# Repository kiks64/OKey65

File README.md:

# Okey65 ortholinear keyboard
<br />This work is licensed under a <a rel="license" href="http://creativecommons.org/licenses/by-nc-sa/4.0/">Creative Commons Attribution-NonCommercial-ShareAlike 4.0 International License</a>.
### _A 65 keys ortholinear keyboard using a qwerty based symetric layout_

The goal of this project is to design an enhanced version of my hand-wired keyboard that I have been using for several years. 
The keyboard has a well-balanced size that allows it to be quite compact while still having all the important keys available on the main layer.
Its layout is quite atypical but very convenient for typing text with accented Latin characters.  

It is based on an Atmega32u4 chip and runs QMK. The switch footprints are 5-pins MX type.
The design is minimalist, not including backlight, but modern : the pcb has no screws and is fully dampened by EVA foam.  
However, not being an electronics professional and this project being my first one, the switches are not hot-swappable since integrating this feature makes the design too complex for my skill level.  

Before continuing, I would like to thank ai03 and Masterzen for their tutorials which made this project possible, as well as all the contributors of the QMK firmware.
<p align="center">
  <br />
  
  &nbsp; &nbsp;
  
</p>

### List of required parts

The keyboard consists of a top plate, a pcb and a bottom plate, all in fr4 and designed on Kicad, as well as a 3d printed frame in resin 8000 (sla) designed on Fusion 360. All these parts were ordered from JLCPCB.
I chose these materials for their reasonable cost, their lightness as well as to obtain a soft typing feeling.   

All the electronic components come from Digikey except the Atmel chip which comes from Aliexpress since it is out of stock at all specialist retailers. The BOM list therefore consists of component references available from Digikey.  

Regarding the switches, I chose Gateron Pro Milky Yellow for their price, their softness and because they are stock lubed, which saves me laborious work.  

Finally, I reused the keycaps from my previous hand-wired keyboard because they come from Signature Plastics and are very expensive.
It is difficult to find a keyset that is perfectly compatible with this keyboard because the caps have to be non sculpted (dsa or xda) and ortholinear sets lack keycaps since they are designed for the Plank and Preonic which are smaller than my keyboard.  

Apart from the Signature Plastics solution, I found two sets that fit perfectly :   
A simple set, entirely white, inexpensive and available immediately: https://fr.aliexpress.com/item/1005003174191494.html (version white with legend)  
If you are not in a hurry, a magnificent set, more expensive and rarely available: https://drop.com/buy/massdrop-x-mito-canvas-xda-custom-keycap-set (alphas/betas set + text ortho/micons ortho set)  

**Aditionnal stuff you will need :**  
An USB type C cable.  
Spray paint and plastic primer : I used Montana Colors mtn94 paint, nice quality, easy to use.  
M2 brass standoffs 10mm : https://aliexpress.com/item/4000314663724.html (fit perfectly).  
M2 flat head screws 10mm : https://aliexpress.com/item/4001072025844.html  
Foam tapes 1x12mm + 3x8mm : https://aliexpress.com/item/33012825553.html  
Foam sheets  2mm : I used this item https://aliexpress.com/item/1005002856054113.html but it is more dense than I expected, maybe not the best option.  
A Double-sided adhesive tape.  
A syringe of solder paste (preferably T5 grade because the usb type c port is tricky to solder) as well as solder wire.  
A hot air rework station, a solder iron, tweezers, a magnifying glass and a cutting tool.  
A lot of patience :)  

### Assembly guide  

To start, heat the frame with a hair dryer and then insert the spacers into it. Once cool, the spacers will be tight enough, no need to add glue.  
Then take care of painting the frame and let it dry well.Sanding may be required before painting.  
Then place the 1mm adhesive foam strip inside the frame as shown in the photo below. 

Cut out the different foams using the top plate and bottom plate as templates :  
Between the top plate and the pcb I used 2 sheets of 2mm that I glued together before cutting them. With 4mm of compact foam for a space between plates of 3mm, soldering the switches was very difficult because I had to compress the foam at the same time. Instead, try to find a sheet of 3mm foam or less dense foam.  
Same observation for the foam between the pcb and the bottom plate, 4mm if good but EVA foam is definitely too dense and it was difficult to close the case the first time.  
A last sheet of 2mm foam glued under the bottom plate as a sole. Here, EVA is perfect and provides a good support for the keyboard and prevents the screw heads from touching the desk.  
Finally, cut strips of 3mm wide and thick self-adhesive foam and stick them all around the top plate.
<p align="center">
  <br />
  
  &nbsp; &nbsp;
  
</p>  

Now it's time to solder the components on the pcb.  
Leave the components in their bag until it is time to place them on the solder paste and be sure of their correct placement. Once out of their bag, it is very difficult to differentiate them so be careful!  
You will have 5 pcb, so also have some spare components in case it goes wrong. If you do not know how to use a hot air station, I advise you to find out before you start.  

Start with the usb receptacle which is the hardest part to solder because the pins are very close. Use very little solder paste to avoid making bridges which are very hard to see and remove.
Do not forget to secure the fixing of the usb receptacle by soldering the through tabs with a soldering iron and soldering wire  
Do the same for the Atmel chip, but this time it's easier and you can put a little more solder paste.  
Finally, put solder paste on all the remaining pads and arrange all your smd components, taking care to respect the polarity of the diodes, and solder them all at the same time.  

Check your welds with a magnifying glass and use a multimeter to check that there are no bridges.  
If everything is ok, it's time to flash the firmware. Instructions are available in the README file of the firmware's folder.  

Finally comes the step of soldering the switches, don't forget the foam between the top plate and the pcb ;)  
Start by soldering a switch at each corner, then one or two in the middle. After that, place all the switches and solder them.  

Plug in your keyboard to test all the keys. If a whole row or column does not work, check that all the pins of the chip are well soldered. If an isolated key does not work, it is likely that the polarities of the associated diode are reversed.  

If everything works, all you have to do is insert the assembly into the frame, add the 4mm foam, place the bottom plate and screw it gently.  
Finally install the caps, connect the usb cable and enjoy!  
If you plan to use accents, set your computer's input method to US International.
  <p align="center">
  <br />
  
  &nbsp; &nbsp;
  
</p>  
<p align="center">
  
  &nbsp; &nbsp;
  
</p>  

Using a wrist rest greatly improves comfort and ergonomics.
I made one with some EVA foam, double sided tape and cloth, the dimensions are 300x80x15mm and that's fine, a little longer would be perfect, like 320-350mm.

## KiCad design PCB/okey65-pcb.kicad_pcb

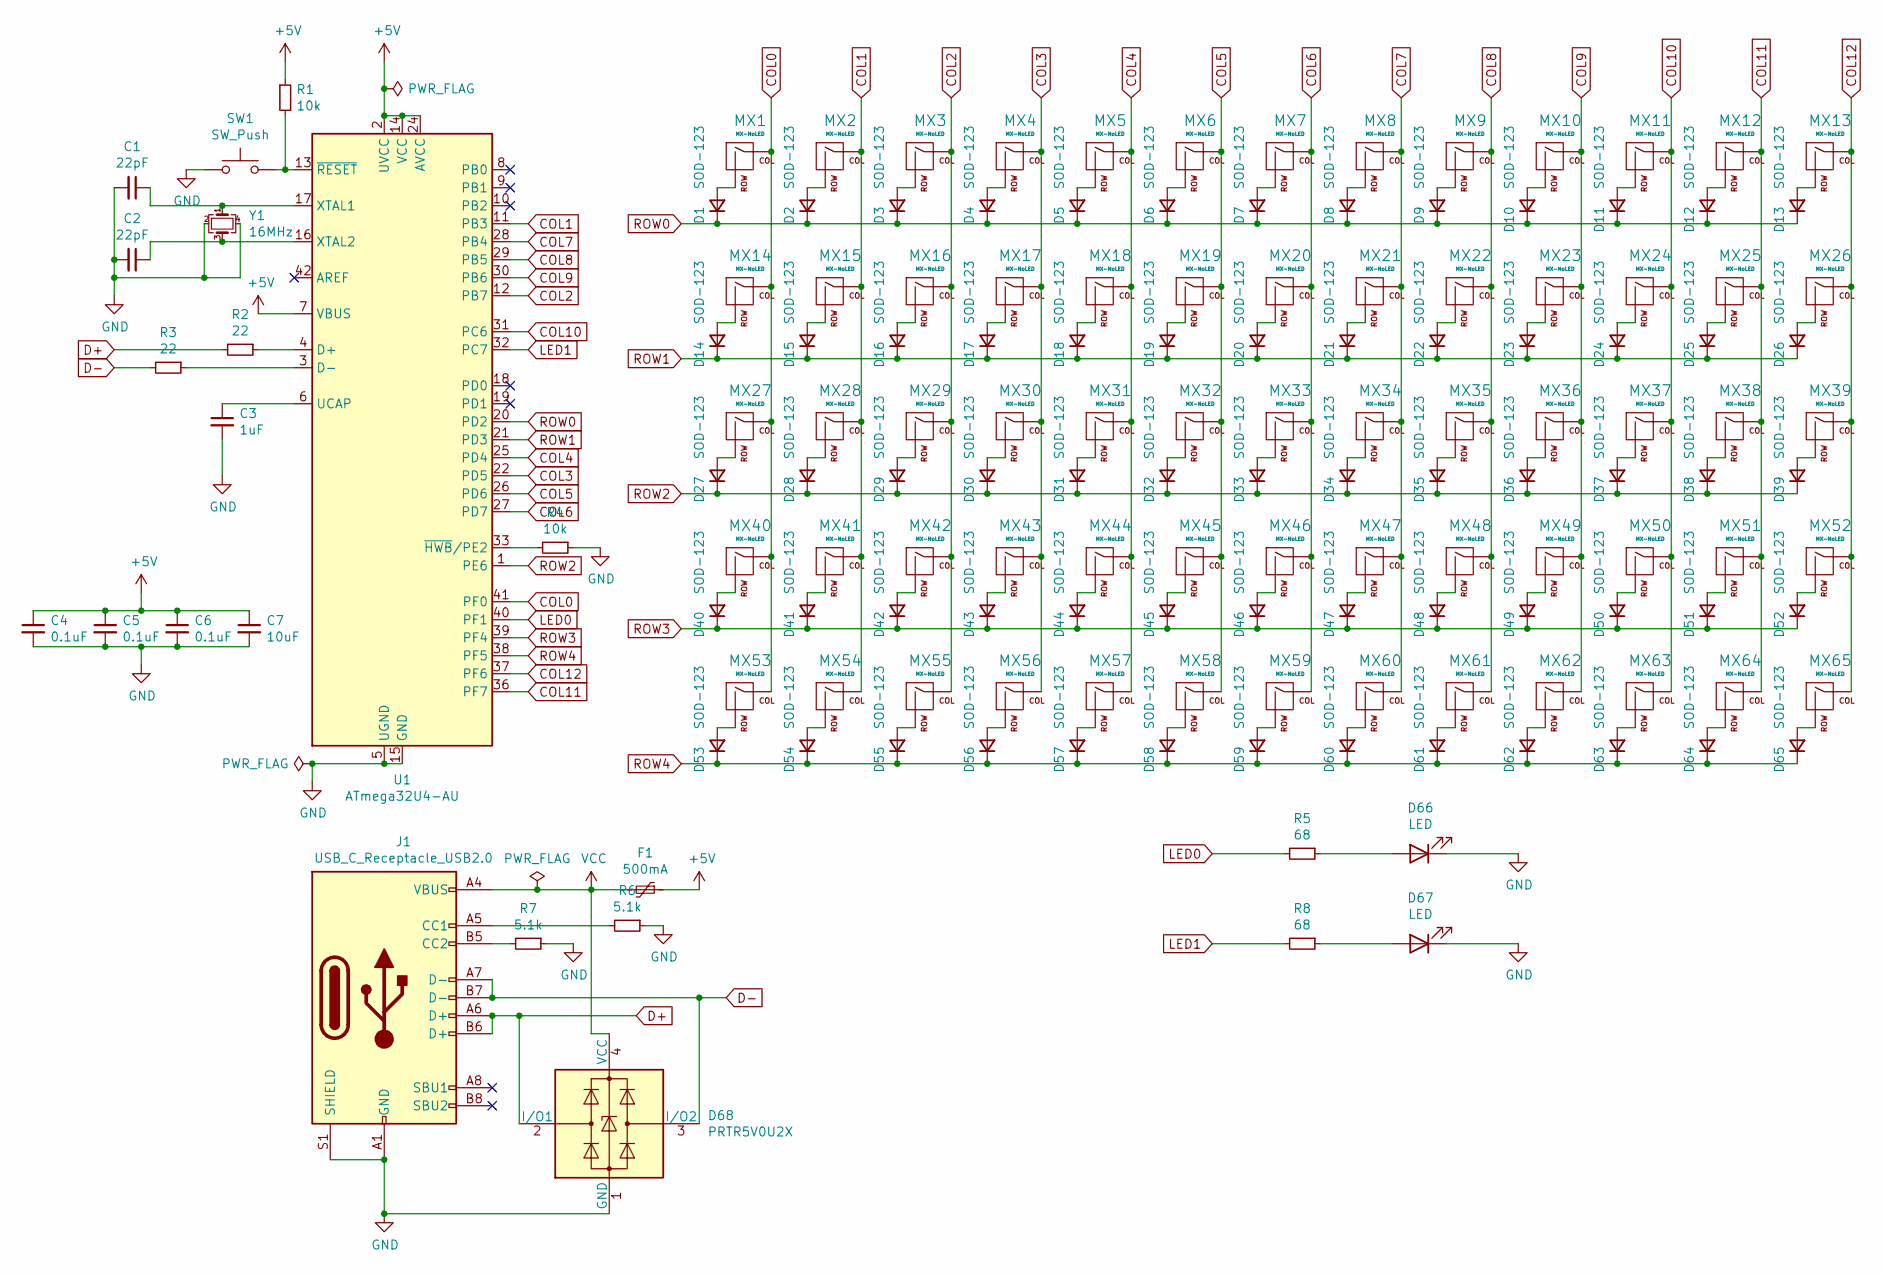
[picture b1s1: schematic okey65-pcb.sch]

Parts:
C1, C2: 22pF; C_0805_2012Metric; LCSC C1804
C3: 1uF; C_0805_2012Metric; LCSC C116352
C4, C5, C6: 0.1uF; C_0805_2012Metric; LCSC C286511
C7: 10uF; C_1206_3216Metric; LCSC C77075
D1, D2, D3, D4, D5, D6, D7, D8, D9, D10, D11, D12, D13, D14, D15, D16, D17, D18, D19, D20, D21, D22, D23, D24, D25, D26, D27, D28, D29, D30, D31, D32, D33, D34, D35, D36, D37, D38, D39, D40, D41, D42, D43, D44, D45, D46, D47, D48, D49, D50, D51, D52, D53, D54, D55, D56, D57, D58, D59, D60, D61, D62, D63, D64, D65: SOD-123; D_SOD-123; LCSC C81598
D66, D67: LED; LED_1206_3216Metric_ReverseMount_Hole1.8x2.4mm; LCSC C401114
D68: PRTR5V0U2X; SOT143B
F1: 500mA; Fuse_1206_3216Metric; LCSC C883125
J1: USB_C_Receptacle_USB2.0; USB_C_Receptacle_Palconn_UTC16-G; LCSC C136423
MX1, MX2, MX3, MX4, MX5, MX6, MX7, MX8, MX9, MX10, MX11, MX12, MX13, MX14, MX15, MX16, MX17, MX18, MX19, MX20, MX21, MX22, MX23, MX24, MX25, MX26, MX27, MX28, MX29, MX30, MX31, MX32, MX33, MX34, MX35, MX36, MX37, MX38, MX39, MX40, MX41, MX42, MX43, MX44, MX45, MX46, MX47, MX48, MX49, MX50, MX51, MX52, MX53, MX54, MX55, MX56, MX57, MX58, MX59, MX60, MX61, MX62, MX63, MX64, MX65: MX-NoLED; MXOnly-1U-NoLED
R1, R4: 10k; R_0805_2012Metric; LCSC C406725
R2, R3: 22; R_0805_2012Metric; LCSC C25295
R5, R8: 68; R_0805_2012Metric; LCSC C17802
R6, R7: 5.1k; R_0805_2012Metric; LCSC C27834
SW1: SW_Push; SKQG-1155865; LCSC C221929
U1: ATmega32U4-AU; TQFP-44_10x10mm_P0.8mm; LCSC C44854
Y1: 16MHz; Crystal_SMD_3225-4Pin_3.2x2.5mm; LCSC C213410

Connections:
+5V: C4.1, C5.1, C6.1, C7.1, F1.1, R1.1, U1.2 (UVCC), U1.7 (VBUS), U1.14 (VCC), U1.24 (AVCC), U1.34 (VCC), U1.44 (AVCC)
COL0: MX1.1 (COL), MX14.1 (COL), MX27.1 (COL), MX40.1 (COL), MX53.1 (COL), U1.41 (PF0)
COL1: MX2.1 (COL), MX15.1 (COL), MX28.1 (COL), MX41.1 (COL), MX54.1 (COL), U1.11 (PB3)
COL2: MX3.1 (COL), MX16.1 (COL), MX29.1 (COL), MX42.1 (COL), MX55.1 (COL), U1.12 (PB7)
COL3: MX4.1 (COL), MX17.1 (COL), MX30.1 (COL), MX43.1 (COL), MX56.1 (COL), U1.22 (PD5)
COL4: MX5.1 (COL), MX18.1 (COL), MX31.1 (COL), MX44.1 (COL), MX57.1 (COL), U1.25 (PD4)
COL5: MX6.1 (COL), MX19.1 (COL), MX32.1 (COL), MX45.1 (COL), MX58.1 (COL), U1.26 (PD6)
COL6: MX7.1 (COL), MX20.1 (COL), MX33.1 (COL), MX46.1 (COL), MX59.1 (COL), U1.27 (PD7)
COL7: MX8.1 (COL), MX21.1 (COL), MX34.1 (COL), MX47.1 (COL), MX60.1 (COL), U1.28 (PB4)
COL8: MX9.1 (COL), MX22.1 (COL), MX35.1 (COL), MX48.1 (COL), MX61.1 (COL), U1.29 (PB5)
COL9: MX10.1 (COL), MX23.1 (COL), MX36.1 (COL), MX49.1 (COL), MX62.1 (COL), U1.30 (PB6)
COL10: MX11.1 (COL), MX24.1 (COL), MX37.1 (COL), MX50.1 (COL), MX63.1 (COL), U1.31 (PC6)
COL11: MX12.1 (COL), MX25.1 (COL), MX38.1 (COL), MX51.1 (COL), MX64.1 (COL), U1.36 (PF7)
COL12: MX13.1 (COL), MX26.1 (COL), MX39.1 (COL), MX52.1 (COL), MX65.1 (COL), U1.37 (PF6)
D+: D68.2 (I/O1), J1.A6 (D+), J1.B6 (D+), R2.2
D-: D68.3 (I/O2), J1.A7 (D-), J1.B7 (D-), R3.2
LED0: R5.2, U1.40 (PF1)
LED1: R8.2, U1.32 (PC7)
unnamed: C1.1, U1.17 (XTAL1), Y1.1
unnamed: C2.1, U1.16 (XTAL2), Y1.3
unnamed: C3.1, U1.6 (UCAP)
unnamed: D1.2 (A), MX1.2 (ROW)
unnamed: D2.2 (A), MX2.2 (ROW)
unnamed: D3.2 (A), MX3.2 (ROW)
unnamed: D4.2 (A), MX4.2 (ROW)
unnamed: D5.2 (A), MX5.2 (ROW)
unnamed: D6.2 (A), MX6.2 (ROW)
unnamed: D7.2 (A), MX7.2 (ROW)
unnamed: D8.2 (A), MX8.2 (ROW)
unnamed: D9.2 (A), MX9.2 (ROW)
unnamed: D10.2 (A), MX10.2 (ROW)
unnamed: D11.2 (A), MX11.2 (ROW)
unnamed: D12.2 (A), MX12.2 (ROW)
unnamed: D13.2 (A), MX13.2 (ROW)
unnamed: D14.2 (A), MX14.2 (ROW)
unnamed: D15.2 (A), MX15.2 (ROW)
unnamed: D16.2 (A), MX16.2 (ROW)
unnamed: D17.2 (A), MX17.2 (ROW)
unnamed: D18.2 (A), MX18.2 (ROW)
unnamed: D19.2 (A), MX19.2 (ROW)
unnamed: D20.2 (A), MX20.2 (ROW)
unnamed: D21.2 (A), MX21.2 (ROW)
unnamed: D22.2 (A), MX22.2 (ROW)
unnamed: D23.2 (A), MX23.2 (ROW)
unnamed: D24.2 (A), MX24.2 (ROW)
unnamed: D25.2 (A), MX25.2 (ROW)
unnamed: D26.2 (A), MX26.2 (ROW)
unnamed: D27.2 (A), MX27.2 (ROW)
unnamed: D28.2 (A), MX28.2 (ROW)
unnamed: D29.2 (A), MX29.2 (ROW)
unnamed: D30.2 (A), MX30.2 (ROW)
unnamed: D31.2 (A), MX31.2 (ROW)
unnamed: D32.2 (A), MX32.2 (ROW)
unnamed: D33.2 (A), MX33.2 (ROW)
unnamed: D34.2 (A), MX34.2 (ROW)
unnamed: D35.2 (A), MX35.2 (ROW)
unnamed: D36.2 (A), MX36.2 (ROW)
unnamed: D37.2 (A), MX37.2 (ROW)
unnamed: D38.2 (A), MX38.2 (ROW)
unnamed: D39.2 (A), MX39.2 (ROW)
unnamed: D40.2 (A), MX40.2 (ROW)
unnamed: D41.2 (A), MX41.2 (ROW)
unnamed: D42.2 (A), MX42.2 (ROW)
unnamed: D43.2 (A), MX43.2 (ROW)
unnamed: D44.2 (A), MX44.2 (ROW)
unnamed: D45.2 (A), MX45.2 (ROW)
unnamed: D46.2 (A), MX46.2 (ROW)
unnamed: D47.2 (A), MX47.2 (ROW)
unnamed: D48.2 (A), MX48.2 (ROW)
unnamed: D49.2 (A), MX49.2 (ROW)
unnamed: D50.2 (A), MX50.2 (ROW)
unnamed: D51.2 (A), MX51.2 (ROW)
unnamed: D52.2 (A), MX52.2 (ROW)
unnamed: D53.2 (A), MX53.2 (ROW)
unnamed: D54.2 (A), MX54.2 (ROW)
unnamed: D55.2 (A), MX55.2 (ROW)
unnamed: D56.2 (A), MX56.2 (ROW)
unnamed: D57.2 (A), MX57.2 (ROW)
unnamed: D58.2 (A), MX58.2 (ROW)
unnamed: D59.2 (A), MX59.2 (ROW)
unnamed: D60.2 (A), MX60.2 (ROW)
unnamed: D61.2 (A), MX61.2 (ROW)
unnamed: D62.2 (A), MX62.2 (ROW)
unnamed: D63.2 (A), MX63.2 (ROW)
unnamed: D64.2 (A), MX64.2 (ROW)
unnamed: D65.2 (A), MX65.2 (ROW)
unnamed: D66.2 (A), R5.1
unnamed: D67.2 (A), R8.1
unnamed: J1.A5 (CC1), R6.2
unnamed: J1.B5 (CC2), R7.2
unnamed: R1.2, SW1.2, U1.13 (~RESET)
unnamed: R2.1, U1.4 (D+)
unnamed: R3.1, U1.3 (D-)
unnamed: R4.2, U1.33 (~HWB~/PE2)
ROW0: D1.1 (K), D2.1 (K), D3.1 (K), D4.1 (K), D5.1 (K), D6.1 (K), D7.1 (K), D8.1 (K), D9.1 (K), D10.1 (K), D11.1 (K), D12.1 (K), D13.1 (K), U1.20 (PD2)
ROW1: D14.1 (K), D15.1 (K), D16.1 (K), D17.1 (K), D18.1 (K), D19.1 (K), D20.1 (K), D21.1 (K), D22.1 (K), D23.1 (K), D24.1 (K), D25.1 (K), D26.1 (K), U1.21 (PD3)
ROW2: D27.1 (K), D28.1 (K), D29.1 (K), D30.1 (K), D31.1 (K), D32.1 (K), D33.1 (K), D34.1 (K), D35.1 (K), D36.1 (K), D37.1 (K), D38.1 (K), D39.1 (K), U1.1 (PE6)
ROW3: D40.1 (K), D41.1 (K), D42.1 (K), D43.1 (K), D44.1 (K), D45.1 (K), D46.1 (K), D47.1 (K), D48.1 (K), D49.1 (K), D50.1 (K), D51.1 (K), D52.1 (K), U1.39 (PF4)
ROW4: D53.1 (K), D54.1 (K), D55.1 (K), D56.1 (K), D57.1 (K), D58.1 (K), D59.1 (K), D60.1 (K), D61.1 (K), D62.1 (K), D63.1 (K), D64.1 (K), D65.1 (K), U1.38 (PF5)
VCC: D68.4 (VCC), F1.2, J1.A4 (VBUS), J1.A9 (VBUS), J1.B4 (VBUS), J1.B9 (VBUS)

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
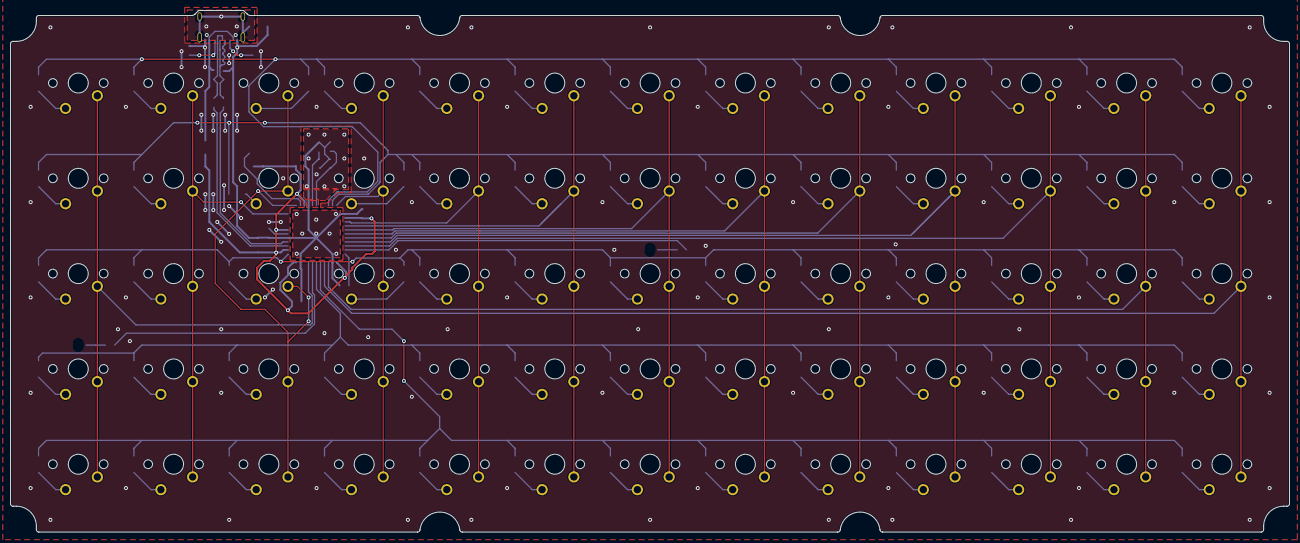
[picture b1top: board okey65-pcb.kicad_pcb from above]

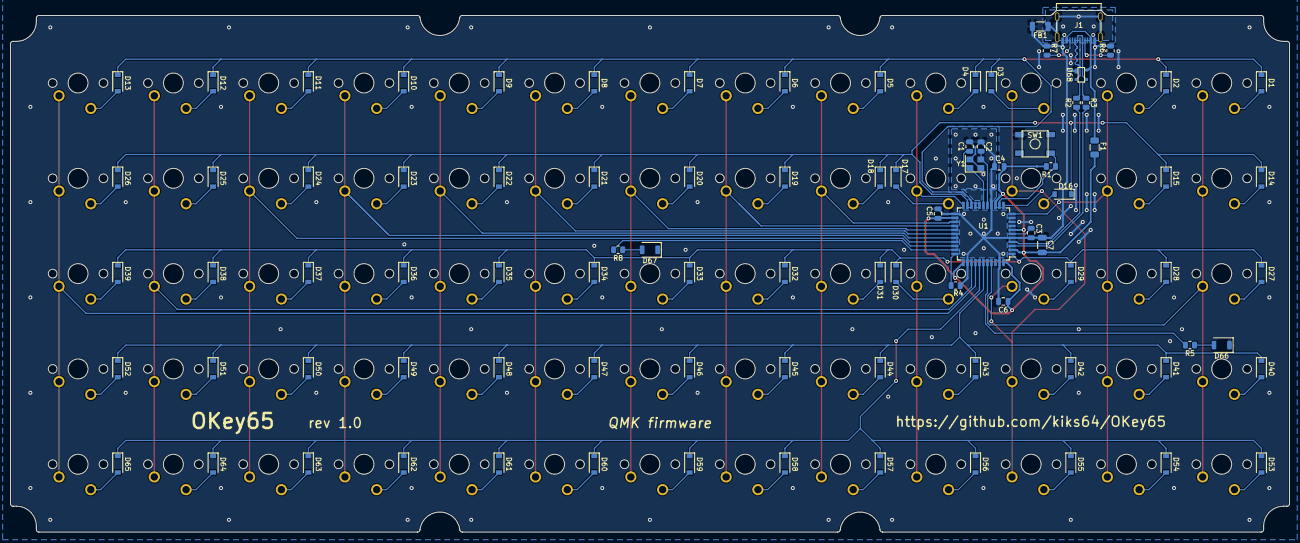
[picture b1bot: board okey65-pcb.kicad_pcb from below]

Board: 2 copper layers, 255.7 x 104.3 mm, 154 parts (89 on the bottom side), 102 nets.

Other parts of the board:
FB1: 60@100MHz; L_1206_3216Metric

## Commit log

2021-12-14 Initialize project
2021-12-14 Add PCB footprint libraries
2021-12-14 MCU circuit shematic
2021-12-14 USB circuit shematic
2021-12-14 Shema completed + pcb matrix
2021-12-15 Place all footprints
2021-12-15 Route core circuits
2021-12-16 Routing complete
2021-12-17 PCB complete
2021-12-20 Hardware almost complete
2021-12-22 General improvements - no ground planes
2022-01-07 v 1.0
2022-01-26 Firmware complete
    Adding firmware + fixing a small issue with the frame
2022-02-03 Firmware update
    Update firmware (macros) and firmware README.
2022-02-06 Firmware update
    Indicator LEDs issue fixed by rewriting the firmware with the officlal QMK environment instead of using kbfirmware.com configurator.
